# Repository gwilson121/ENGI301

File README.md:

# Repository for ENGI301 Course Work

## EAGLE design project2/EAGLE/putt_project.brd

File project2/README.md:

This is the github folder for Project 2. Project 2 entailed creating a Printed Circuit Board (PCB) design of Project 1. My PCB included an LCD display, four buttons, a USB jack for audio input, and cable inputs for the two IR sensors. The board has four layers with two power polygons, and one ground layer. The buttons are placed such that the record and history buttons are side by side at the bottom of the board while the history scroll buttons are stacked on top of each other at the far right side ofthe board.

The functionality of the board is as follows:

It is a device that measures the speed at which a golf ball approaches the hole. It will be positioned directly in front of the cup, slightly offset from the line of the putt. Used on flat putting surfaces to help with speed/distance control.

The device will provide visual and audible feedback. The ball speed will be visible on a small display screen, and a speaker will inform the user of the quality of the putt based on its speed:

Slow speeds: ”Too slow!”
Fast speeds: “Too fast!”
Perfect speed: “Perfect putt!”

The device will utilize IR sensors, a screen display, a speaker, buttons, and the Pocket Beagle to achieve this functionality.

The screen will display a history of the speeds of the recorded putts, and two buttons will be used to scroll up and down the list of putt speeds. All speeds are in cm/s.

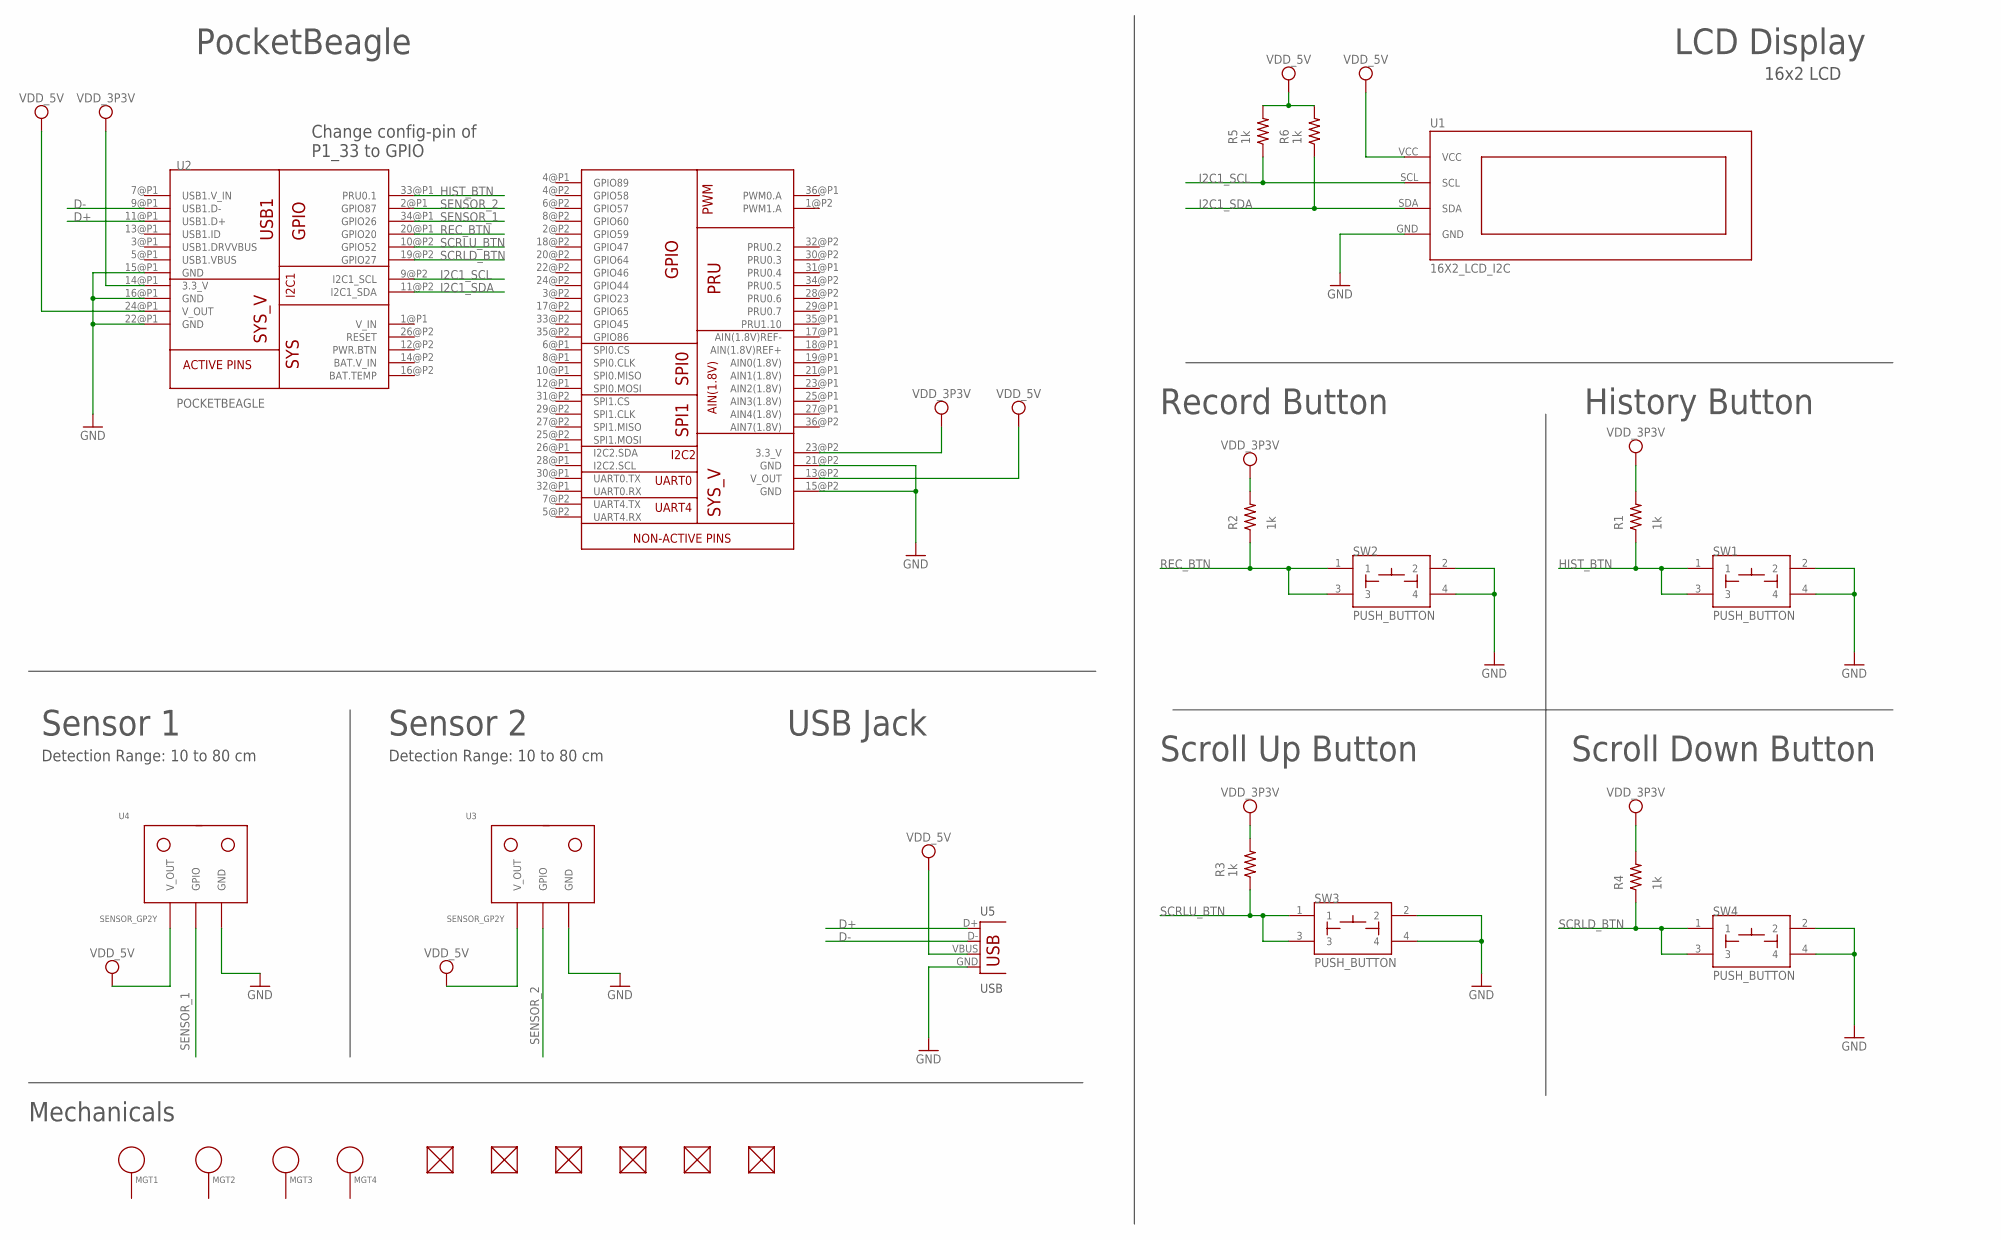
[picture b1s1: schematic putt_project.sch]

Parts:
FUD1, FUD2, FUD3, FUD4, FUD5, FUD6: FIDUCIAL; FIDUCIAL_40MIL
MGT1, MGT2, MGT3, MGT4: MOUNTING_HOLE
R1, R2, R3, R4, R5, R6: 1k; R0603
SW1, SW2, SW3, SW4: PUSH_BUTTON; BUTTON_12.5MM
U1: 16X2_LCD_I2C
U2: POCKETBEAGLE
U3, U4: SENSOR_GP2Y; SENSOR_IR
U5: USB; USB-A-H

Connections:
D+: U2.11@P1 (USB1.D+), U5.D+
D-: U2.9@P1 (USB1.D-), U5.D-
GND: SW1.2, SW1.4, SW2.2, SW2.4, SW3.2, SW3.4, SW4.2, SW4.4, U1.GND, U2.15@P1 (GND), U2.15@P2 (GND), U2.16@P1 (GND), U2.21@P2 (GND), U2.22@P1 (GND), U3.GND, U4.GND, U5.GND
HIST_BTN: R1.1, SW1.1, SW1.3, U2.33@P1 (PRU0.1)
I2C1_SCL: R5.1, U1.SCL, U2.9@P2 (I2C1_SCL)
I2C1_SDA: R6.1, U1.SDA, U2.11@P2 (I2C1_SDA)
REC_BTN: R2.1, SW2.1, SW2.3, U2.20@P1 (GPIO20)
SCRLD_BTN: R4.1, SW4.1, SW4.3, U2.19@P2 (GPIO27)
SCRLU_BTN: R3.1, SW3.1, SW3.3, U2.10@P2 (GPIO52)
SENSOR_1: U2.34@P1 (GPIO26), U4.GPIO
SENSOR_2: U2.2@P1 (GPIO87), U3.GPIO
VDD_3P3V: R1.2, R2.2, R3.2, R4.2, U2.14@P1 (3.3_V), U2.23@P2 (3.3_V)
VDD_5V: R5.2, R6.2, U1.VCC, U2.13@P2 (V_OUT), U2.24@P1 (V_OUT), U3.PWR (V_OUT), U4.PWR (V_OUT), U5.VBUS

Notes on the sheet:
PocketBeagle
LCD Display
Sensor 1
Sensor 2
USB Jack
Record Button
History Button
Scroll Up Button
Scroll Down Button
Change config-pin of P1_33 to GPIO
Detection Range: 10 to 80 cm
16x2 LCD
USB
Mechanicals

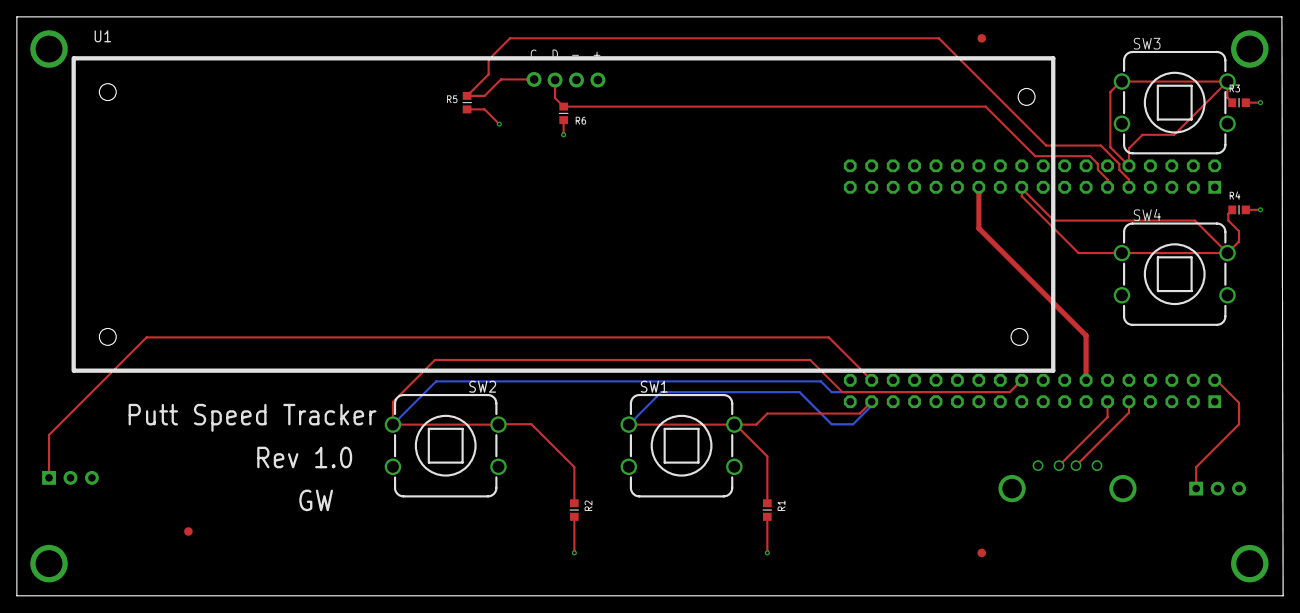
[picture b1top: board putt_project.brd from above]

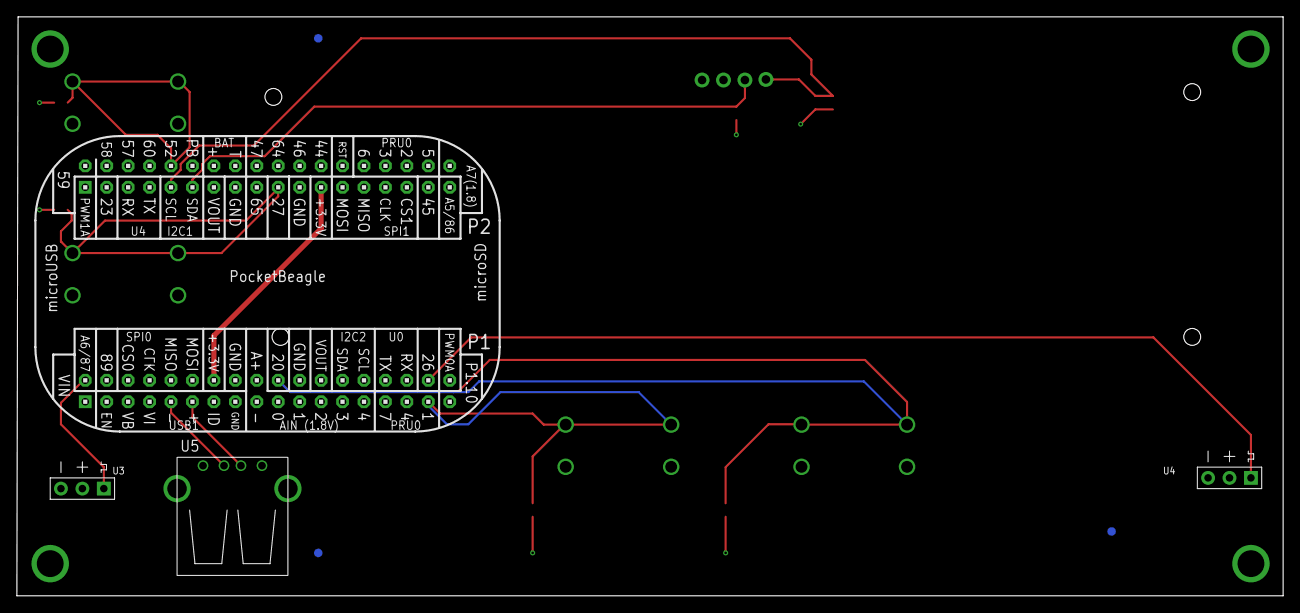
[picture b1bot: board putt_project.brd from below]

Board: 4 copper layers, 150.0 x 68.6 mm, 25 parts (7 on the bottom side), 13 nets.

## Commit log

2020-09-25 First Commit for Calculator
2020-09-29 2nd Commit for Calculator
2020-09-29 3rd Calculator Commit
2020-09-29 Blink LED
2020-10-29 Initial Commit for Putt Project
2020-11-07 Adding putter files
2020-11-07 Adding run script
2020-11-07 Adding README
2020-11-07 Updating README
2020-11-07 Update files
2020-11-08 Update Config Pins
